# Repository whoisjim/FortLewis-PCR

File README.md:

FLC-PCR is a field deployable and low cost PCR thermocycler developed by students at Fort Lewis College. Polymerase chain reaction (PCR) is the process of duplicating a strand of DNA millions of times. After the DNA has been amplified analysis can be performed to detect pathogens and other DNA related characteristics. Performing PCR on a strand of DNA involves placing the sample in a chemical solution. Then repeating the raising and lowering the temperature duplicates the DNA. Raising the temperature splits the strands and lowering the temperature allows the chemicals to reform the other half of each DNA strand.

## Student Members

- James Ferguson
- Jesse Duran
- Wesley Killinen
- Gavin Wakefield
- Farjana Showme

## Faculty Advisors

- Jason Wagner
- Caroline Kulesza
- Christie Chatterley
- Yiyan Li

## Folder Descriptions

- **CAD:** SOLIDWORKS design files for the the lid and heating block.
- **Circuts:** EAGLE PCB design files for the  PCB microcontroller.
- **DataRecordingAndGraphing:** Recorded data and python scripts for graphing and analysis.
- **Papers:** Project documentation that was presented at weekly meetings or conferences etc.
- **Parts:** Datasheets for components.
- **Software:** The programs that run on the FLC-PCR system.

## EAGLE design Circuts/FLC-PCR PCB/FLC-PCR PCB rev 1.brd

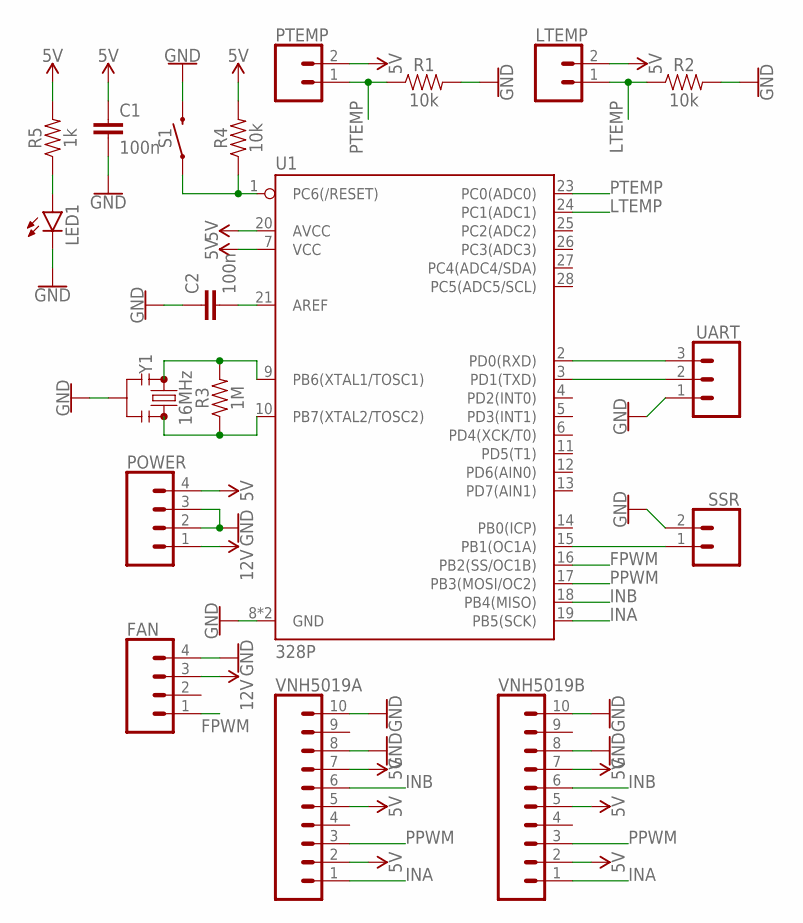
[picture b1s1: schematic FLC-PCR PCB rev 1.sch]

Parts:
C1, C2: 100n; C025-050X050
FAN: CONN_04PTH; 1X04
LED1: LED5MM
LTEMP: CONN_02; 1X02
POWER: CONN_04PTH; 1X04
PTEMP: CONN_02; 1X02
R1, R2, R4: 10k; AXIAL-0.3
R3: 1M; AXIAL-0.3
R5: 1k; AXIAL-0.3
S1: MOMENTARY-SWITCH-SPST-PTH-6.0MM; TACTILE_SWITCH_PTH_6.0MM
SSR: CONN_02; 1X02
U1: 328P; DIP28
UART: CONN_03; 1X03
VNH5019A, VNH5019B: CONN_10"; 1X10
Y1: 16MHz; RESONATOR-PTH-7.6X3.8

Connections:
5V: C1.1, LTEMP.2, POWER.4, PTEMP.2, R4.P$2 (2), R5.P$2 (2), U1.7 (VCC), U1.20 (AVCC), VNH5019A.2, VNH5019A.5, VNH5019A.7, VNH5019B.2, VNH5019B.5, VNH5019B.7
12V: FAN.3, POWER.1
FPWM: FAN.1, U1.16 (PB2(SS/OC1B))
GND: C1.2, C2.1, FAN.4, LED1.K (C), POWER.2, POWER.3, R1.P$2 (2), R2.P$2 (2), S1.3 (2), SSR.2, U1.8 (GND), U1.22 (GND), UART.1, VNH5019A.8, VNH5019A.10, VNH5019B.8, VNH5019B.10, Y1.2
INA: U1.19 (PB5(SCK)), VNH5019A.1, VNH5019B.1
INB: U1.18 (PB4(MISO)), VNH5019A.6, VNH5019B.6
LTEMP: LTEMP.1, R2.P$1 (1), U1.24 (PC1(ADC1))
unnamed: U1.2 (PD0(RXD)), UART.3
unnamed: U1.3 (PD1(TXD)), UART.2
unnamed: R3.P$2 (2), U1.9 (PB6(XTAL1/TOSC1)), Y1.1
unnamed: R3.P$1 (1), U1.10 (PB7(XTAL2/TOSC2)), Y1.3
unnamed: R4.P$1 (1), S1.1, U1.1 (PC6(/RESET))
unnamed: LED1.A, R5.P$1 (1)
unnamed: C2.2, U1.21 (AREF)
unnamed: SSR.1, U1.15 (PB1(OC1A))
PPWM: U1.17 (PB3(MOSI/OC2)), VNH5019A.3, VNH5019B.3
PTEMP: PTEMP.1, R1.P$1 (1), U1.23 (PC0(ADC0))

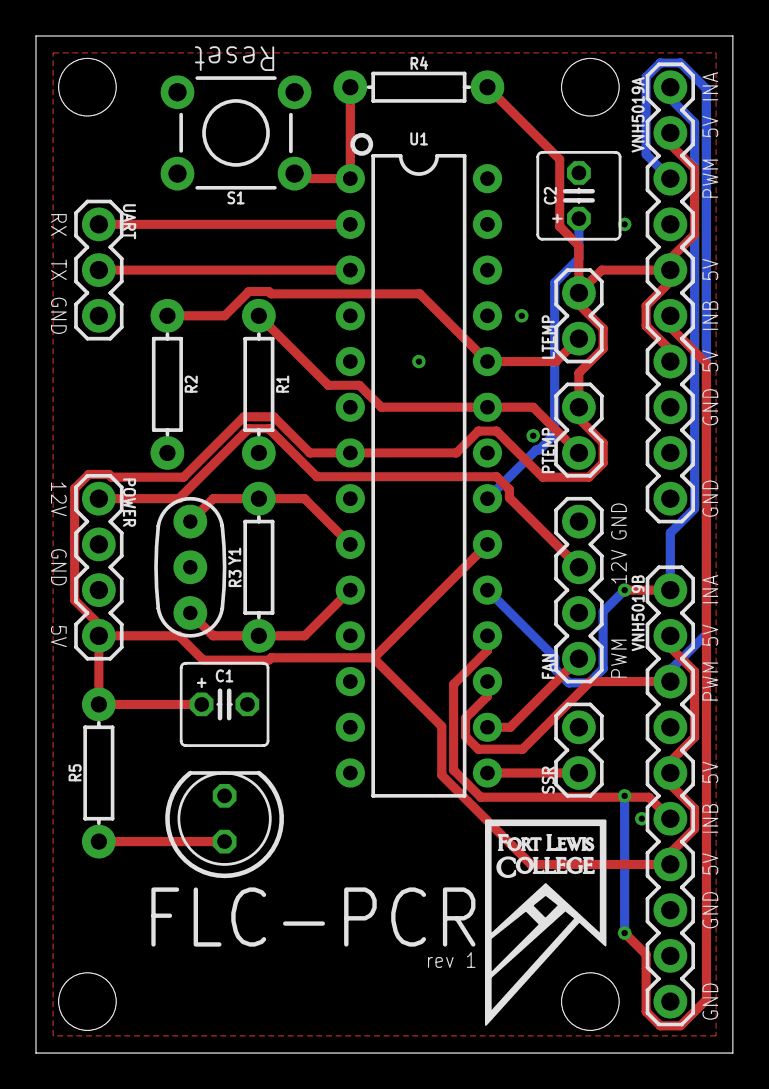
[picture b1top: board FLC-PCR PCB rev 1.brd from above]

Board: 2 copper layers, 38.7 x 56.5 mm, 19 parts (0 on the bottom side), 17 nets.

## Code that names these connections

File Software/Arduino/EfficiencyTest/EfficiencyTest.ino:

#include <math.h>
const int inA = 13; // pin connected to INA on VHN5019
const int inB = 12; // pin connected to INB on VHN5019
const int ppwm = 11; // pin connected to PWM on VHN5019
const int fpwm = 10; // pin connected to PWM on fan
const int thermP = A0; // pin connected to thermal resistor neetwork. see elegooThermalResistorSch.png

bool power = false; // software on/off

double peltierPWM = 0; // the PWM signal * curent direction to be sent to curent drivers for peltier

float avgPTemp = 0; // last average for peltier temperature
int avgPTempSampleSize = 10; // sample size for peltier temperature moving average

double targetPeltierTemp = 30; // the tempature the system will try to move to, in degrees C
double currentPeltierTemp; // the tempature curently read from the thermoristor connected to thermP, in degrees C

// class for creating a pid system
class pid {
  private:
  double kp; // higher moves faster
  double ki; // higher fixes ofset and faster
  double kd; // higher settes faster but creastes ofset
  double kAmbiant; // experimental, fixes ofset?, may remove. leave at zero if unshure
  unsigned long currentTime, lastTime; // the time in millisecconds of this timesep and the last timestep
  double pError, lError, iError, dError; // error values for pid calculations. p: porportional, l: last, i: integerl, d: derivitive
    
  public:
  pid (double proportionalGain = 1, double integralGain = 0, double derivativeGain = 0) {
    kp = proportionalGain; // higher moves faster
    ki = integralGain; // higher fixes ofset and faster
    kd = derivativeGain; // higher settes faster but creastes ofset and amplifies noise
  }
  
  double calculate(double currentTemp, double targetTemp){ // gets tempature and performs pid calculation returns error in degrees C
    lastTime = currentTime;
    currentTime = millis();
    lError = pError;
    pError = targetTemp - currentTemp;
    iError = pError * (double)(currentTime - lastTime);
    dError = (pError - lError) / (double)(currentTime - lastTime);
    return kp * pError + ki * iError + kd * dError;
  }
  void setKp(float value) {
    kp = value;
  }
  void setKi(float value) {
    ki = value;
  }
  void setKd(float value) {
    kd = value;
  }
};

// for creating a tempature sensor
// includes noise reduction
// call resetTemp() before a series of getTemp() calls
// see elegooThermalResistorSch.png for wireing
class TempSensor {
  private:
  int pin;
  double temp;
  double lastK;
  
  public:
  TempSensor(int iPin) { 
    pin = iPin; // the pin that conected to the tempature network
  }
  
  void resetTemp() { // resets saved privois tempature, nessasary if it has been a while since last getTemp()
    int tempReading = analogRead(pin);
    double tempK = log(10000.0 * ((1024.0 / tempReading - 1)));
    lastK = 1 / (0.001129148 + (0.000234125 + (0.0000000876741 * tempK * tempK )) * tempK );
  }

  double getTemp() { // returns the tempature from thermoristor connected to thermP in degrees C, includes noise reduction
    static double spike0u;
    int tempReading = analogRead(pin);
    double tempK = log(10000.0 * ((1024.0 / tempReading - 1)));
    tempK = 1 / (0.001129148 + (0.000234125 + (0.0000000876741 * tempK * tempK )) * tempK ); // kelvin

    //Serial.print(tempK - 273.15);
    //Serial.print(" ");
    
    // noise peak removal
    
    if (tempK - lastK > 0.5 + abs(lastK -299.15) * 0.1) {
      if (spike0u == 0) {
        spike0u = tempK - lastK;
      }
      tempK -= spike0u;
    } else {
      spike0u = 0;
    }

    if (tempK - lastK < -10) {
      tempK += spike0u;
      spike0u = 0;
    }
    
    lastK = tempK;
    
    return (tempK - 273.15); // convert kelvin to celcius
  }
};

// setup pieltier tempature sensor
TempSensor peltierT(thermP);

// setup pieltier PID
pid peltierPID(5, 0.8, 6000);

bool finished = false;
bool start = false;

void setup() {
  // setup serial
  Serial.begin(9600);
  while (!Serial) {
    ; // wait for serial port to connect. Needed for native USB port only
  }

  // setup pins
  pinMode(inA, OUTPUT);
  pinMode(inB, OUTPUT);
  pinMode(ppwm, OUTPUT);
  pinMode(fpwm, OUTPUT);
  pinMode(thermP, INPUT);

  // set initial pin state to off
  digitalWrite(inA, LOW);
  digitalWrite(inB, LOW);
  analogWrite(ppwm, 0);
  analogWrite(fpwm, 0);

  peltierT.resetTemp();
}

void loop() {
  currentPeltierTemp = peltierT.getTemp(); // read pieltier temp
  avgPTemp = ((avgPTempSampleSize - 1) * avgPTemp + currentPeltierTemp) / avgPTempSampleSize; // average input with the last 9 inputs
  peltierPWM = peltierPID.calculate(avgPTemp, targetPeltierTemp); // calculate pid and set to output
  peltierPWM = min(255, max(-255, peltierPWM)); // clamp output between -255 and 255

  if (digitalRead(7) == HIGH) {
    start = true;
  }

  if (start) {
    peltierPWM = 63;
  } else {
    peltierT.resetTemp();
  }

  float pI = analogRead(A1) * 0.065168; // for two driver boards
  float pV = peltierPWM * (15 / 255.0);
  
  // for graphing system state
  Serial.print(avgPTemp);
  Serial.print(" ");
  Serial.print(pV);
  Serial.print(" ");
  Serial.print(pI);
  Serial.print("\n");

  if (currentPeltierTemp > 65) {
    finished = true;
  }

  if (finished) {
    digitalWrite(inA, LOW);
    digitalWrite(inB, LOW);
    analogWrite(fpwm, 1024);
    analogWrite(ppwm, 0);
    return;
  }
  
  if (currentPeltierTemp > 150) {// shut off system if over 150 degrees for safety
    digitalWrite(inA, LOW);
    digitalWrite(inB, LOW);
    analogWrite(fpwm, 1024);
    analogWrite(ppwm, 0);
    return;
  }

  // convert pieltierDelta to pwm, inA, inB, and fan signals
  analogWrite(ppwm, abs(peltierPWM));
  if (peltierPWM > 0) {
    digitalWrite(inA, HIGH);
    digitalWrite(inB, LOW);
    analogWrite(fpwm, 0);
  } else {
    digitalWrite(inA, LOW);
    digitalWrite(inB, LOW);
    analogWrite(fpwm, 255);
  }
}

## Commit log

2019-11-11 Fixed noise reduction problem
2019-11-12 Fixed noise reduction more
    probably still some problems.
2019-11-16 Added some notes
2019-11-16 Added 12711-9L31-09CQ datasheet
2019-11-22 Added peltier signal smoothing, removed PID extra thing.
2019-11-22 updated tuneing
2019-12-01 finished exept for com data transfer
2019-12-02 Added arduino comunication
2019-12-02 added commands for changing tempature and power
2019-12-06 Rename PCRDebug.py to PCRDebugUi.py
2019-12-12 Add files via upload
    PCR heating block
2019-12-12 Create 3TempsFormat
2019-12-12 Rename 3TempsFormat to 3TempsFormat.txt
2019-12-12 Updated GUI and added configurable cycles
2019-12-13 Removed arbitrary scaling
2019-12-13 Minor changes
2019-12-20 Added comments
2020-01-03 Recorded data for efficiency tests
2020-01-03 for recording efficiency data
2020-01-03 added link to product page
2020-01-03 Graphed efency data
    Has errors
2020-01-06 rerun tests and fixed error
2020-01-06 fixed error
2020-01-06 retested with runtime
2020-01-06 replacing incorrect data
2020-01-06 Rendered and updated graph
2020-01-06 Updated colors
2020-01-06 Fixed labeling error
2020-01-07 notes on voltages
2020-01-07 updated graph
2020-01-08 Dada logging is more flexable
2020-01-08 added limits and current monitoring
2020-01-08 updated scripts and created cycleing power graph
2020-01-10 Recorded new data
2020-01-14 Rename PCR_Code_Jesse.ino to Arduino/PCR_Code_Jesse/PCR_Code_Jesse.ino
2020-01-14 merged lid and peltier scripts
2020-01-15 fixed and ajusted a few things
2020-01-16 ran first 40 cycle test
2020-01-16 recored more 40 cycle data
2020-01-16 Heated lid data
2020-01-17 Heatedlidgraph
2020-01-17 Ran first real PCR reaction
2020-01-17 updated PID settings
2020-01-17 did some ananisys
2020-01-18 Made some figures
2020-01-18 did some ananysys
2020-01-19 ajusted graphs
2020-01-20 changed pin
2020-01-24 Add files via upload
    Visio files for FLCPCR figures
2020-01-28 updated to show lid temp
2020-02-03 did some updates
2020-02-03 Orginised git
2020-02-03 Created READMEs
2020-02-04 Added timestamp to start of file
2020-02-07 Recorded some calabration data might be bad
2020-02-07 did calabration analisys data is definatly bad
2020-02-09 recorded new temperature data
2020-02-10 Did Temperature curve fit
2020-02-10 finished curve fit script
2020-02-13 did calabration with Biorad block
2020-02-14 Applied Temperature calabration
2020-02-16 Created Bash script for installing SDL2
2020-02-16 created sdl2 test file
2020-02-16 added test font and image
2020-02-18 Started RPI GUI
2020-02-18 Created som basic padding textures
2020-02-20 Started UI classes
2020-02-22 small work done
2020-02-22 Added cycle step icons
2020-02-23 Created Cycle step UI
2020-02-23 renamed some files
2020-02-23 added temperature icon
2020-02-23 created cycle UI class
2020-02-24 Finished cycle Ui movement
2020-02-27 formatted ui.h and fixed pointer ishues
2020-02-27 added the ability to add or delete cycle steps
2020-02-29 Started Keypad
2020-03-04 twaeked some things
2020-03-06 added button and key classes
2020-03-06 added comments to main.cpp
2020-03-12 started state managment
2020-03-22 Added gui indicator light images
2020-03-25 drew progress bar texture
2020-04-03 redid graphics
2020-04-03 More graphic redos
2020-04-03 added a grey padding
2020-04-04 added recycle bin texture
2020-04-18 screenshot test
2020-04-21 updated software, commented files and took screenshots fo report
2020-04-22 renamed screenshots
2020-05-07 fixed floating point problems
2020-05-09 Began work on the load Menu
2020-05-09 added previous state functionality, file display, and fixed Text has zero width for //
2020-05-09 finished save and load menu functionality still needs polish to be consifered finished
2020-05-09 Rendamed variables for consistancy
2020-05-09 added caps functionality
2020-05-09 added units to cycle step
2020-05-10 added ETA and removed saving and loading while experiment is running
2020-05-10 added save reminder
2020-05-10 added are you sure popups
2020-05-10 split save button into save and saveAs
2020-05-10 setup run flcpcr at boot
2020-05-10 drew letters for main menu logo
2020-05-11 added main menu title and animation
2020-05-11 cleaned up main menu animation
2020-05-11 added keys to keybord, centered button and key text, added warning to running unsaved experement, seperated load and save menus
2020-05-11 major changes to save menu
2020-05-12 updated casp functionality
2020-05-12 added Inconsolata-Bold font
2020-05-12 added more fonts, fixed letters color palate, added folder icon
2020-05-12 changed fonts
2020-05-12 took screenshot for refrence
2020-05-12 drew backspace icon
2020-05-12 changed 'de' to an icon for backspace keys
2020-05-12 took a bunch of screenshots
2020-05-12 added texture and font deletion and removed screenshots
2020-05-12 removed boot text
2020-05-13 addeed mouce support
2020-05-13 ficed mouce editor pan
2020-05-13 swiched experiment path to relative
2020-05-14 fixed experiment editor deconstructor
2020-05-18 Updated serial comunication to work with the PCR-UI
2020-05-19 fixed step time problem and updated protocall for PCRControl.ino
2020-05-19 added compile for linux desktop
2020-05-19 added verbose state mode
2020-05-19 updated filtering may be too much
2020-05-21 started work in fixing PCRControl PID, Renamed Raspberry Pi folder to UI APP, Updated PCRDebugUI to somewhat work still dont reccomend using
2020-05-21 added FLC-PCR PCB rev 1
2020-05-21 updated READMEs
2020-05-21 fixed step timing ishue
2020-05-26 added the ability to navigate sub folders
2020-05-27 added ability to delete folders
2020-06-09 recorded data peltier degradation evaluation, curent modules show 0% - 30% degredation
2020-06-10 added new folder button and fixed same file/folder name problems
2020-06-30 Started work on multy threadding serial comunication, should be a sutable workaround for the delays, needs to be tested
2020-09-08 started physical layout and modeling for NEMA enclosure
2020-09-10 added solidwork files for hollow and solid heating block
2020-09-10 Worked on NEMA enclosure
2020-09-24 finished first revision of lid
2021-02-19 took some solidworks screenshots
2021-02-19 added photos of nema enclosure
2021-02-19 added update presentations
2021-02-19 added update presentation
2021-03-03 added integral gain reset on step change, orginized microcontroller code, modified pid
2021-03-03 made small change to lid heating
2021-03-04 finished serial and new logger
2021-03-05 small PID changes
2021-08-20 fixed incorrect link
2025-06-16 smaller stablity range.cpp
2025-06-16 include timestamps in serial.cpp
2025-06-16 include timestamps
2025-06-17 include time
2025-06-17 2 datapoints/sec
2026-01-23 Added student contributors
2026-01-24 Updated TemperatureSensor class
    Added calculated Steinhart-Hart model coefficients to get better calibrated thermistor readings
    https://www.thinksrs.com/downloads/programs/therm%20calc/ntccalibrator/ntccalculator.html
2026-01-24 Updated PID class
    Optimized PID controller with signal filtering and improved error handling.
2026-01-24 Updated PID Controller
    Conditional PID values calibrated using the Ziegler–Nichols tuning method
2026-01-25 BOM with parts and prices

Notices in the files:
parts and their libraries:
SparkFun-Connectors: Licensing: Creative Commons ShareAlike 4.0 International - https://creativecommons.org/licenses/by-sa/4.0
